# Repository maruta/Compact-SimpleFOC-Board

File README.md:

# Compact SimpleFOC Controller Board

This repository contains design data for a BLDC motor controller board composed of:

* RP2040 (Controller)
* TMC6300 (Driver)
* MT6835 (Magnetic Angle Sensor)
* INA240 (Current Sense Amplifier)

and mainly designed for a tiny inverted pendulm project.

## Disclaimer

The information and design files in this repository are provided "as is" without warranty of any kind, express or implied. We make no guarantees regarding the functionality or reliability of these designs. Users assume full responsibility for the application and use of these files. Any commercial application of these designs is at the user's own risk.

## Description

The board is designed primarily for the SimpleFOC library, with an emphasis on easy customization of the software to suit your application.

The RP2040 component in this design is compatible with the Raspberry Pi Pico, minus the USB connector. It can be programmed using the Arduino IDE with the [Raspberry Pi Pico Arduino core](https://github.com/earlephilhower/arduino-pico), using the [Raspberry Pi Debug Probe](https://www.raspberrypi.com/products/debug-probe/).

### Board Specifications
- Voltage Range: 2-5.5 V
- Maximum Current: 2 A (1.4 Arms)

### Motor Compatibility
- The board has been tested with the RCTIMER GBM2804 motor.

### Connector Details

- J1: RP2040 SWD Connector (3-pin JST SH connector)
  - Pin 1: SWCLK
  - Pin 2: GND
  - Pin 3: SWDIO
- J2: Motor Connector (not populated; 2.54 mm)
  - Pin 1: Motor Phase U
  - Pin 2: Motor Phase V
  - Pin 3: Motor Phase W
- J3: Power and Interface Connector
  - 4-pin JST SH Connector
  - compatible with Qwiic
  - Logic voltage is 3.3 V
  - Pin assign
    - Pin 1: Ground (GND)
    - Pin 2: Positive Voltage (V+)
    - Pin 3: GPIO4 (I2C0 SDA / UART1_TX)
    - Pin 4: GPIO5 (I2C0 SCL / UART1_RX)

## Manufacturing

Use the `production` folder for manufacturing this board with [JLCPCB](https://jlcpcb.com/).

### JLCPCB Ordering Guide

PCB Manufacturing Specifications:
- File to Upload: `gerber.zip`
- Key Settings:
  - Via Covering: Epoxy Filled & Capped
  - Min. via hole size/diameter: 0.2mm(0.3/0.35mm)

PCB Assembly Details:
- Key Settings:
  - Assembly Side: Both Sides
  - Confirm Parts Placement: Required
  - Board Depaneling & Edge Rail: As per requirement
- Required Files: `BOM: bom.csv`, `CPL: positions.csv`
- Components not automatically selected are specified by LCSC part numbers in the circuit files.
- RT6150 and TMC6300 need to be ordered through Global Sourcing Parts Service due to their unavailability at JLCPCB. *Note that the quantity required may be more than the actual quantity to be implemented.*

## Circuit Editing

* Created using KiCAD v7.

* Component models from [Ultra Librarian](https://www.ultralibrarian.com/) are not included due to licensing. Download these models to edit the circuit. See README.md in the following folders for more information:

  - ul_RT6150B-33GQW
  - ul_TMC6300-LA
  - ul_W25Q16JVUXIQ

* Use [Fabrication Toolkit](https://github.com/bennymeg/JLC-Plugin-for-KiCad) to generate . Generated files are stored in the `production` folder.

## License

Files in this repository are under the MIT License.

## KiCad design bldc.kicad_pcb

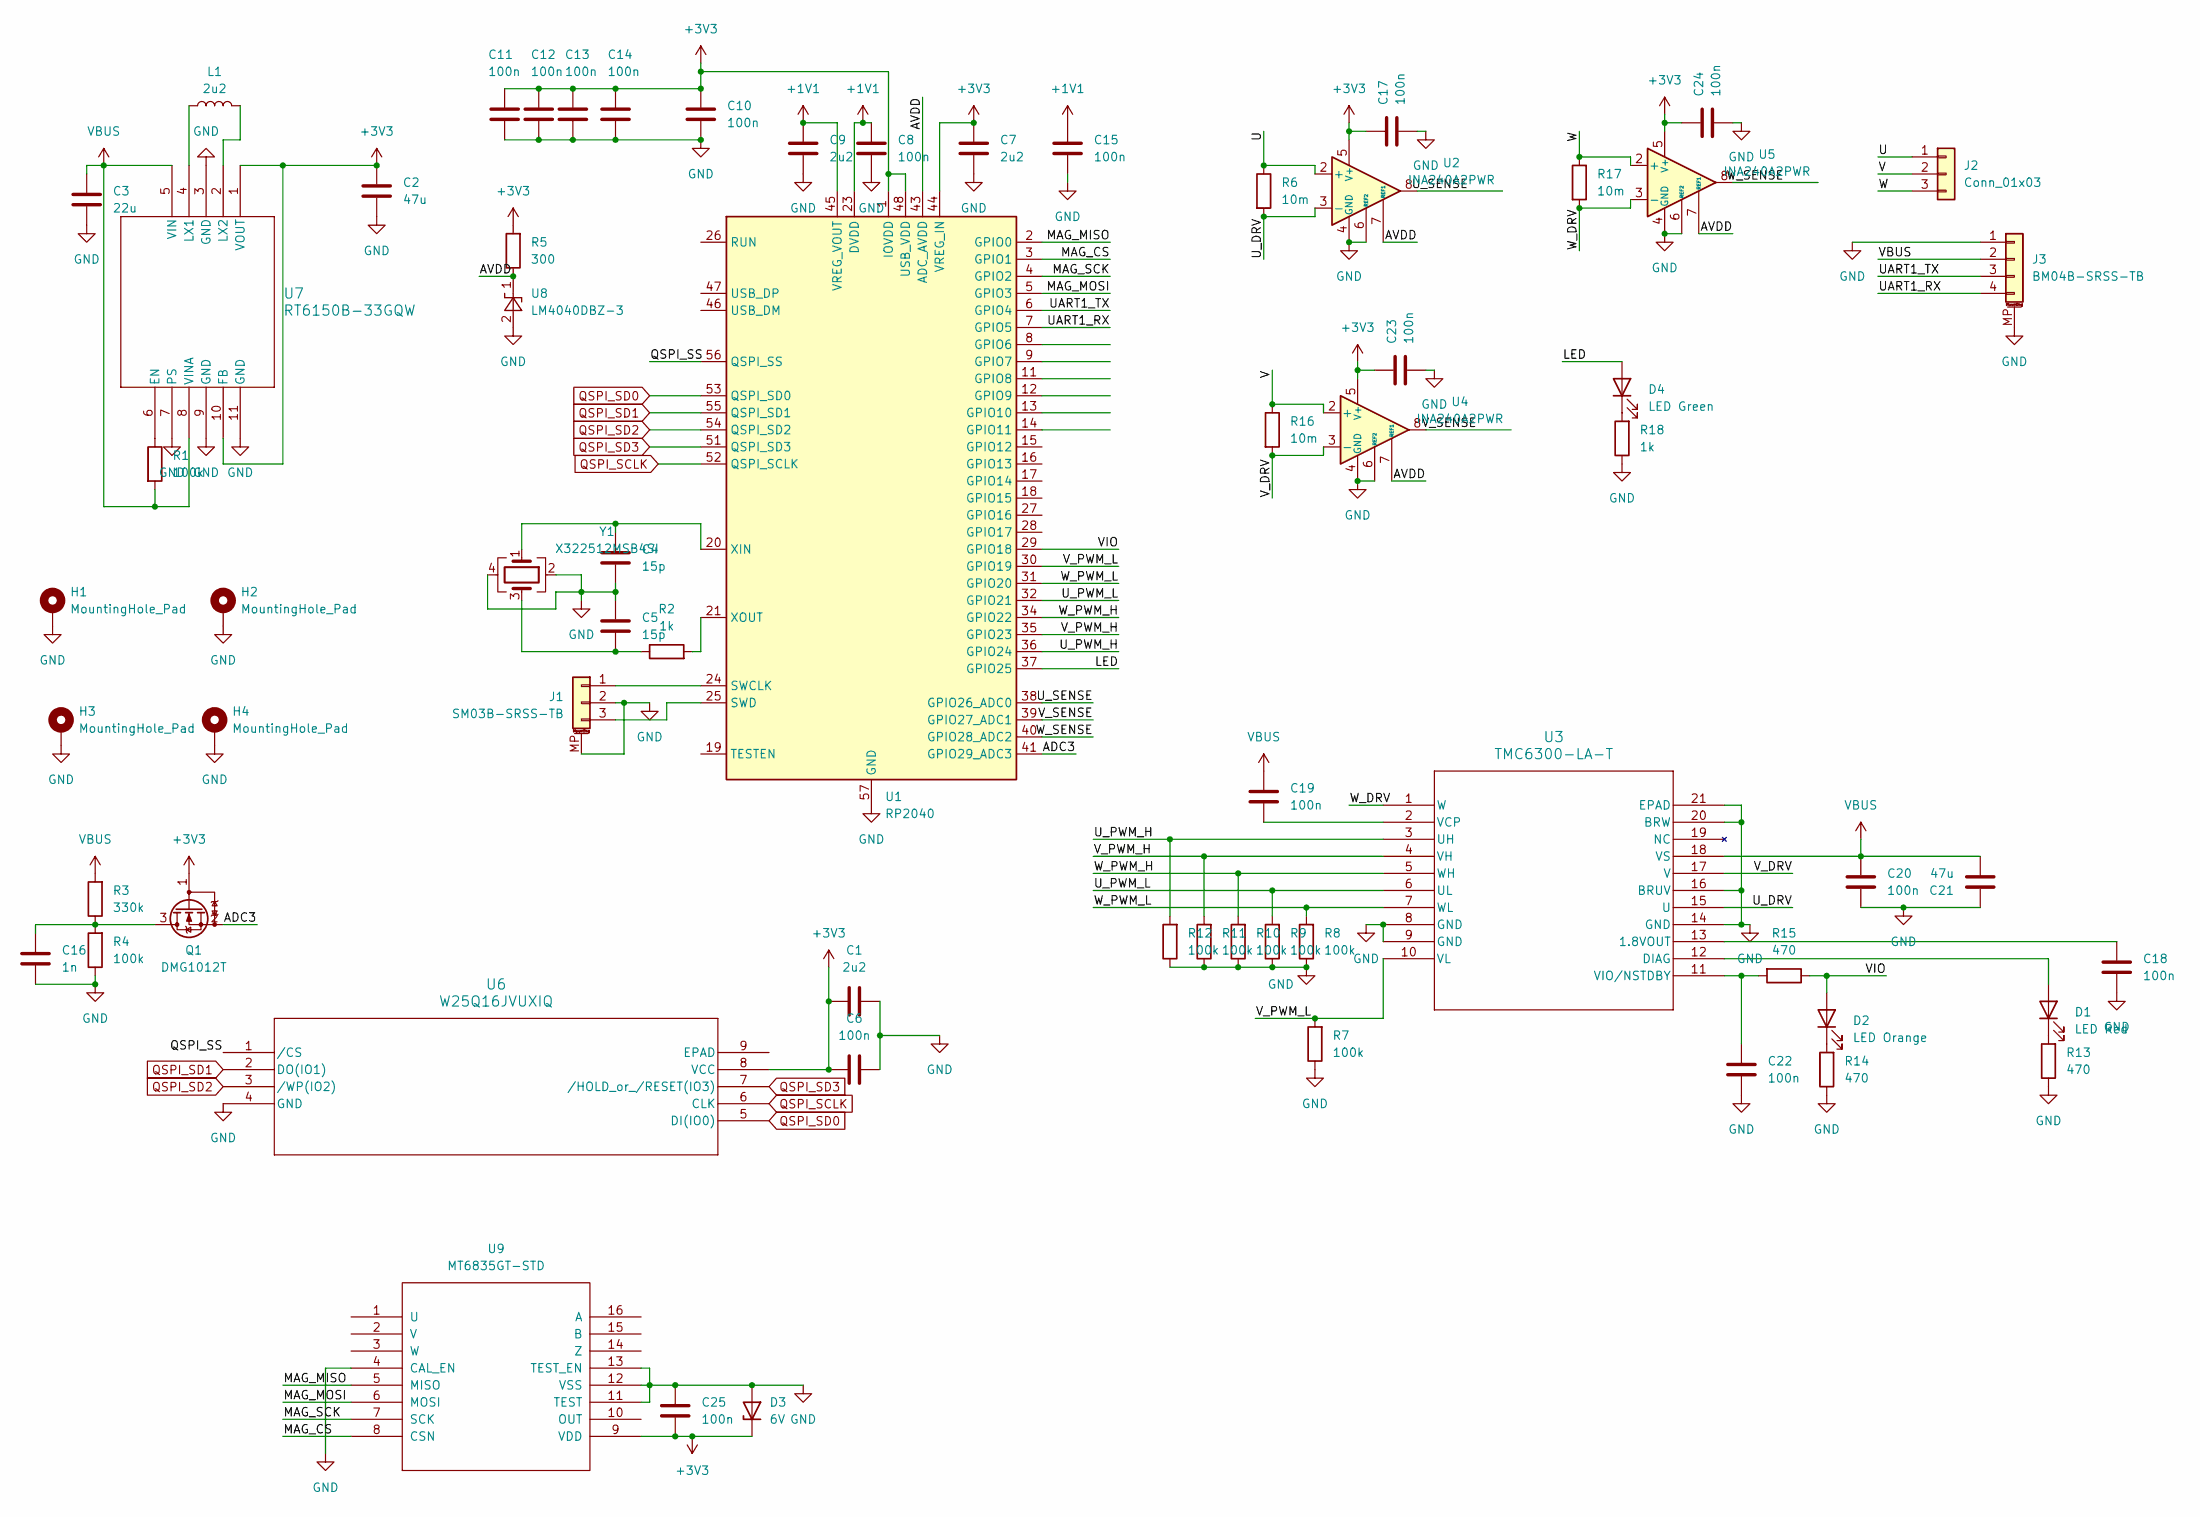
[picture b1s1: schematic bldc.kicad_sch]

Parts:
C1, C7, C9: 2u2; C_0402_1005Metric
C2: 47u; C_0805_2012Metric
C3: 22u; C_0805_2012Metric
C4, C5: 15p; C_0201_0603Metric
C6, C8, C10, C11, C12, C13, C14, C15, C17, C18, C19, C20, C22, C23, C24, C25: 100n; C_0201_0603Metric
C16: 1n; C_0201_0603Metric
C21: 47u; C_1210_3225Metric
D1: LED Red; LED_0805_2012Metric; LCSC C84256
D2: LED Orange; LED_0805_2012Metric; LCSC C84262
D3: 6V; D_SOD-123; JLCPCB Rotation Offset 180
D4: LED Green; LED_0805_2012Metric; LCSC C84260
H1, H2, H3, H4: MountingHole_Pad; MountingHole_2.2mm_M2_Pad_Via
J1: SM03B-SRSS-TB; JST_SH_SM03B-SRSS-TB_1x03-1MP_P1.00mm_Horizontal
J2: Conn_01x03; PinHeader_1x03_P2.54mm_Vertical
J3: BM04B-SRSS-TB; JST_SH_BM04B-SRSS-TB_1x04-1MP_P1.00mm_Vertical
L1: 2u2; L_Changjiang_FNR5020S
Q1: DMG1012T; SOT-523
R1, R4, R7, R8, R9, R10, R11, R12: 100k; R_0402_1005Metric
R2, R18: 1k; R_0402_1005Metric
R3: 330k; R_0402_1005Metric
R5: 300; R_0402_1005Metric
R6, R16, R17: 10m; R_0805_2012Metric
R13, R14, R15: 470; R_0402_1005Metric
U1: RP2040; QFN-56-1EP_7x7mm_P0.4mm_EP3.2x3.2mm
U2, U4, U5: INA240A2PWR; TSSOP-8_4.4x3mm_P0.65mm; JLCPCB Rotation Offset 90
U3: TMC6300-LA-T; QFN20_3x3_TRI
U6: W25Q16JVUXIQ; W25Q16JVUXIQ_WIN; JLCPCB Rotation Offset -90
U7: RT6150B-33GQW; 10-WFDFN-EP_RIT-M
U8: LM4040DBZ-3; SOT-23
U9: MT6835GT-STD; TSSOP-16_4.4x5mm_P0.65mm; JLCPCB Rotation Offset 90
Y1: X322512MSB4SI; Crystal_SMD_3225-4Pin_3.2x2.5mm

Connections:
+1V1: C8.2, C9.2, C15.2, U1.23 (DVDD), U1.45 (VREG_VOUT), U1.50 (DVDD)
+3V3: C1.1, C2.1, C6.1, C7.2, C10.2, C11.2, C12.2, C13.2, C14.2, C17.2, C23.2, C24.2, C25.1, D3.1 (K), Q1.1 (G), R5.2, U1.1 (IOVDD), U1.10 (IOVDD), U1.22 (IOVDD), U1.33 (IOVDD), U1.42 (IOVDD), U1.44 (VREG_IN), U1.48 (USB_VDD), U1.49 (IOVDD), U2.5 (V+), U4.5 (V+), U5.5 (V+), U6.8 (VCC), U7.1 (VOUT), U7.10 (FB), U9.9 (VDD)
/ADC3: Q1.2 (S), U1.41 (GPIO29_ADC3)
/AVDD: R5.1, U1.43 (ADC_AVDD), U2.7 (REF1), U4.7 (REF1), U5.7 (REF1), U8.1 (K)
/LED: D4.2 (A), U1.37 (GPIO25)
/MAG_CS: U1.3 (GPIO1), U9.8 (CSN)
/MAG_MISO: U1.2 (GPIO0), U9.5 (MISO)
/MAG_MOSI: U1.5 (GPIO3), U9.6 (MOSI)
/MAG_SCK: U1.4 (GPIO2), U9.7 (SCK)
/QSPI_SS: U1.56 (QSPI_SS), U6.1 (/CS)
/U: J2.1, R6.1, U2.2 (+)
/UART1_RX: J3.4, U1.7 (GPIO5)
/UART1_TX: J3.3, U1.6 (GPIO4)
/U_DRV: R6.2, U2.3 (-), U3.15 (U)
/U_PWM_H: R12.2, U1.36 (GPIO24), U3.3 (UH)
/U_PWM_L: R9.2, U1.32 (GPIO21), U3.6 (UL)
/U_SENSE: U1.38 (GPIO26_ADC0), U2.8
/V: J2.2, R16.1, U4.2 (+)
/VIO: D2.2 (A), R15.1, U1.29 (GPIO18)
/V_DRV: R16.2, U3.17 (V), U4.3 (-)
/V_PWM_H: R11.2, U1.35 (GPIO23), U3.4 (VH)
/V_PWM_L: R7.2, U1.30 (GPIO19), U3.10 (VL)
/V_SENSE: U1.39 (GPIO27_ADC1), U4.8
/W: J2.3, R17.1, U5.2 (+)
/W_DRV: R17.2, U3.1 (W), U5.3 (-)
/W_PWM_H: R10.2, U1.34 (GPIO22), U3.5 (WH)
/W_PWM_L: R8.2, U1.31 (GPIO20), U3.7 (WL)
/W_SENSE: U1.40 (GPIO28_ADC2), U5.8
GND: C1.2, C2.2, C3.2, C4.2, C5.1, C6.2, C7.1, C8.1, C9.1, C10.1, C11.1, C12.1, C13.1, C14.1, C15.1, C16.1, C17.1, C18.1, C20.1, C21.2, C22.1, C23.1, C24.1, C25.2, D3.2 (A), H1.1, H2.1, H3.1, H4.1, J1.2, J1.MP (MountPin), J3.1, J3.MP (MountPin), R4.1, R7.1, R8.1, R9.1, R10.1, R11.1, R12.1, R13.1, R14.1, R18.1, U1.57 (GND), U2.1 (GND), U2.4 (GND), U2.6 (REF2), U3.8 (GND), U3.9 (GND), U3.14 (GND), U3.16 (BRUV), U3.20 (BRW), U3.21 (EPAD), U4.1 (GND), U4.4 (GND), U4.6 (REF2), U5.1 (GND), U5.4 (GND), U5.6 (REF2), U6.4 (GND), U7.3 (GND), U7.7 (PS), U7.9 (GND), U7.11 (GND), U8.2 (A), U9.4 (CAL_EN), U9.11 (TEST), U9.12 (VSS), U9.13 (TEST_EN), Y1.2, Y1.4
unnamed: C5.2, R2.1, Y1.3
unnamed: D1.2 (A), U3.12 (DIAG)
unnamed: D1.1 (K), R13.2
unnamed: D2.1 (K), R14.2
unnamed: D4.1 (K), R18.2
unnamed: J1.1, U1.24 (SWCLK)
unnamed: J1.3, U1.25 (SWD)
unnamed: C16.2, Q1.3 (D), R3.1, R4.2
unnamed: C4.1, U1.20 (XIN), Y1.1
unnamed: R2.2, U1.21 (XOUT)
unnamed: C18.2, U3.13 (1.8VOUT)
unnamed: C19.1, U3.2 (VCP)
unnamed: C22.2, R15.2, U3.11 (VIO/NSTDBY)
unnamed: R1.1, U7.6 (EN)
unnamed: L1.1, U7.4 (LX1)
unnamed: L1.2, U7.2 (LX2)
QSPI_SCLK: U1.52 (QSPI_SCLK), U6.6 (CLK)
QSPI_SD0: U1.53 (QSPI_SD0), U6.5 (DI(IO0))
QSPI_SD1: U1.55 (QSPI_SD1), U6.2 (DO(IO1))
QSPI_SD2: U1.54 (QSPI_SD2), U6.3 (/WP(IO2))
QSPI_SD3: U1.51 (QSPI_SD3), U6.7 (/HOLD_or_/RESET(IO3))
VBUS: C3.1, C19.2, C20.2, C21.1, J3.2, R1.2, R3.2, U3.18 (VS), U7.5 (VIN), U7.8 (VINA)

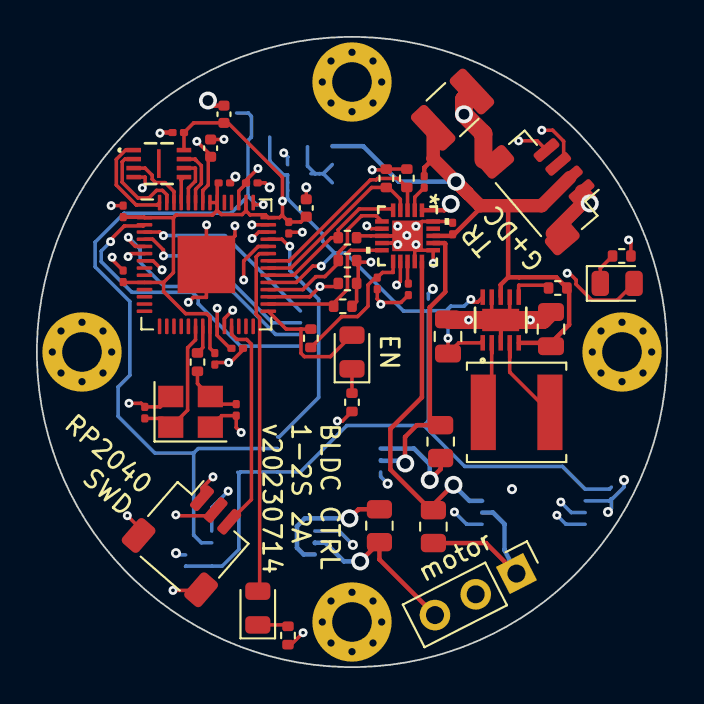
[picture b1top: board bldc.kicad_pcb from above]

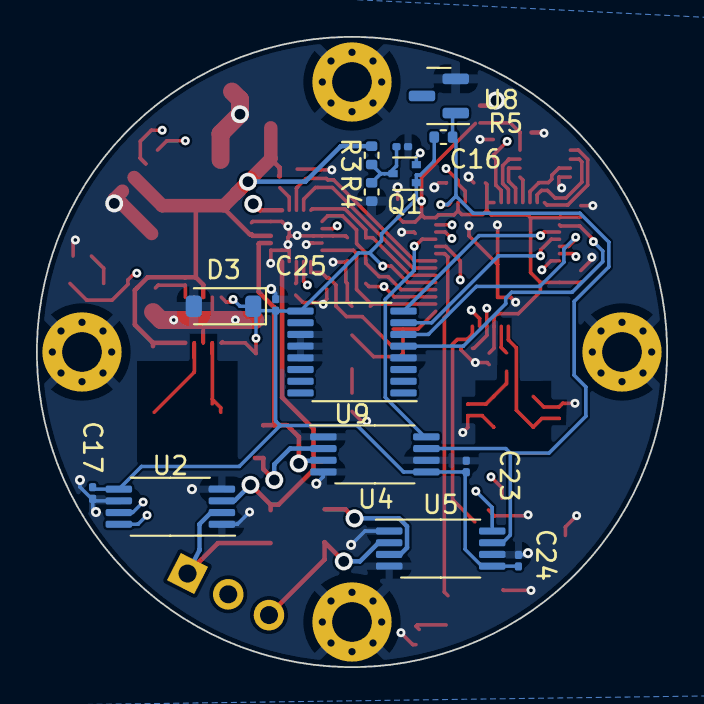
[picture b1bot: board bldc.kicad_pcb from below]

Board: 4 copper layers, 35.0 x 35.0 mm, 66 parts (15 on the bottom side), 51 nets.

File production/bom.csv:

Designator,Footprint,Quantity,Value,LCSC Part #
"C1, C7, C9",0402,3,2u2,
"C10, C11, C12, C13, C14, C15, C17, C18, C19, C20, C22, C23, C24, C25, C6, C8",0201,16,100n,
C16,0201,1,1n,
C2,0805,1,47u,
C21,1210,1,47u,
C3,0805,1,22u,
"C4, C5",0201,2,15p,
D1,0805,1,LED Red,C84256
D2,0805,1,LED Orange,C84262
D3,D_SOD-123,1,6V,
D4,0805,1,LED Green,C84260
J1,JST_SH_SM03B-SRSS-TB_1x03-1MP_P1.00mm_Horizontal,1,SM03B-SRSS-TB,
J3,JST_SH_BM04B-SRSS-TB_1x04-1MP_P1.00mm_Vertical,1,BM04B-SRSS-TB,
L1,L_Changjiang_FNR5020S,1,2u2,
Q1,SOT-523,1,DMG1012T,
"R1, R10, R11, R12, R4, R7, R8, R9",0402,8,100k,
"R13, R14, R15",0402,3,470,
"R16, R17, R6",0805,3,10m,
"R18, R2",0402,2,1k,
R3,0402,1,330k,
R5,0402,1,300,
U1,QFN-56-1EP_7x7mm_P0.4mm_EP3.2x3.2mm,1,RP2040,
"U2, U4, U5",TSSOP-8_4.4x3mm_P0.65mm,3,INA240A2PWR,
U3,QFN20_3x3_TRI,1,TMC6300-LA-T,
U6,W25Q16JVUXIQ_WIN,1,W25Q16JVUXIQ,
U7,10-WFDFN-EP_RIT-M,1,RT6150B-33GQW,
U8,SOT-23,1,LM4040DBZ-3,
U9,TSSOP-16_4.4x5mm_P0.65mm,1,MT6835GT-STD,
Y1,Crystal_SMD_3225-4Pin_3.2x2.5mm,1,X322512MSB4SI,

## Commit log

2023-12-02 Create LICENSE
